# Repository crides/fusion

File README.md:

# Fusion

My travel board. Uses minimum spacing with choc mini (PG1232) and Cirque touchpad. It's meant to be folded for easy packing for traveling/going to classes. It's called fusion because the halves are now "fused" together (all my previous boards have been split).

The following picture shows how it's originally assembled:

You can find the caps [here](https://github.com/crides/sqdg). They are printed with the MJF Nylon process at JLCPCB.

The 2 extra pinky keys on the right side are different because I forgot about them when designing and printing the keycaps. Those keys are for steno, and like [the `fissure`](https://github.com/crides/fissure/) this includes [embedded stenograpy](https://github.com/crides/steno/).

The keymap is basically the same as [on the fissure](https://github.com/crides/fissure/?tab=readme-ov-file#latest-keymap) with a little difference in how the gaming and alternative layout layers are toggled.

One extra small feature it has is a PWM controlled RGB LED, which I use to display [LED widgets](https://github.com/zmkfirmware/zmk/issues/1003) on.

You can find a recent-ish configuration for this board [here](https://github.com/crides/zmk/tree/fusion-led-c-config/).

With the 350mAh battery on the board, this lasted me ~5 months of usage (it could've been even longer, the battery started out not on full charge (~3.8V)).

The board measures 148 x 79.5 x 21mm when it's folded (23mm thick if you include the bumpons, and 133mm long if the last 2 keys are cut off, like in the current state (see the bottom of this page)), which fits into a small bag. I carry this with my Pixel 5a in my big sweatpants pocket for quite a while. I would just go to places, take out the keeb and my phone, unfold it and work with Termux.

All parts are generated from Python, some using [solidff](https://github.com/crides/solidff), some using [CadQuery](https://github.com/CadQuery/cadquery/), depending on when the part was designed. The only parts actually used are `hinge1`, `hinge2` and `touchpad-holder`.

Includes JLCPCB BOM ([`bom.csv`](bom.csv)) and POS ([`pos.csv`](pos.csv)) files for PCBA.

---

Here's the board after almost 11 months of usage (right before 2023):

Main differences:
- The trackpad is in a really weird spot. I knew this in the design phase, but didn't have much idea of how to fix it. So it's taken out. 
- A solar charging circuit with a Li-ion supercapacitor is added, replacing the battery and its charging circuit. The current supercap is 150F (!), which is equivalent to about 40mAh. This was to be done on another version of the board, but a small test circuit was fabbed instead, and that was used here with a fair amount of bodging. Now I can say the fusion board is (well can be) powered by fusion! (a.k.a. solar powered)
- There's a crack on the screen. The adhesive I used didn't cover the whole screen area, and once I pressed on the top left corner too hard, where the adhesive also didn't cover and left some empty space, and it cracked :(.

---

Here it is after 1 year:

Somehow the supercap doesn't seem to do well with the cold, so I swapped to the old small battery. Tried out a larger Cirque touchpad, by basically shifting the screen to the left side though a bunch of wires.

---

Here's what it looks like after 16 months:

The screen's completely broken, with the ribbon cable half "cut" (no idea how that happened). The trackpad location is better, but still pretty useless for my use cases (I use it 95% on top of my laptop keyboard most of the time, and the touchpad is right there, with more ready-to-be-used gestures. So touchpads and solar panels are gone. Nothing interesting to see here...

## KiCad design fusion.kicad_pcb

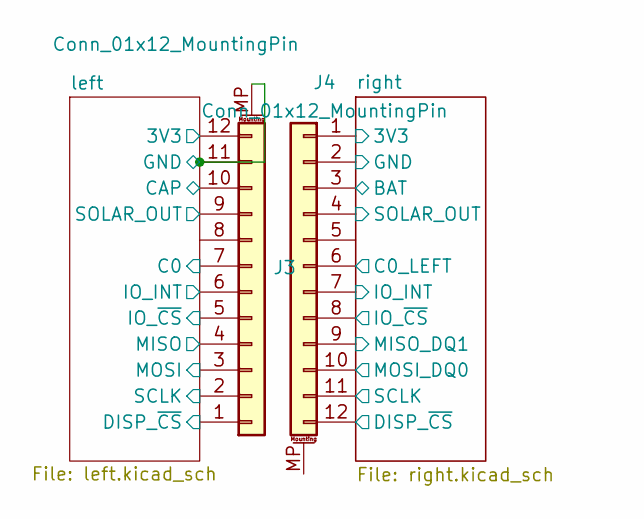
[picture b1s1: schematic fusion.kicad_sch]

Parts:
J3, J4: Conn_01x12_MountingPin; Hirose_FH12-12S-0.5SH_1x12-1MP_P0.50mm_Horizontal

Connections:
/left/3V3: J3.12; also elsewhere on the board
/left/C0: J3.7; also elsewhere on the board
/left/CAP: J3.10; also elsewhere on the board
/left/DISP_~CS: J3.1; also elsewhere on the board
/left/GND: J3.11, J3.MP (MountPin); also elsewhere on the board
/left/IO_INT: J3.6; also elsewhere on the board
/left/IO_~CS: J3.5; also elsewhere on the board
/left/MISO: J3.4; also elsewhere on the board
/left/MOSI: J3.3; also elsewhere on the board
/left/SCLK: J3.2; also elsewhere on the board
/left/SOLAR_OUT: J3.9; also elsewhere on the board
/right/3V3_nRF: J4.1; also elsewhere on the board
/right/BAT: J4.3; also elsewhere on the board
/right/C0_LEFT: J4.6; also elsewhere on the board
/right/DISP_~CS: J4.12; also elsewhere on the board
/right/IO_INT: J4.7; also elsewhere on the board
/right/IO_~CS: J4.8; also elsewhere on the board
/right/MISO_DQ1: J4.9; also elsewhere on the board
/right/MOSI_DQ0: J4.10; also elsewhere on the board
/right/SCLK: J4.11; also elsewhere on the board
/right/SOLAR_OUT: J4.4; also elsewhere on the board
GND: J4.2; also elsewhere on the board

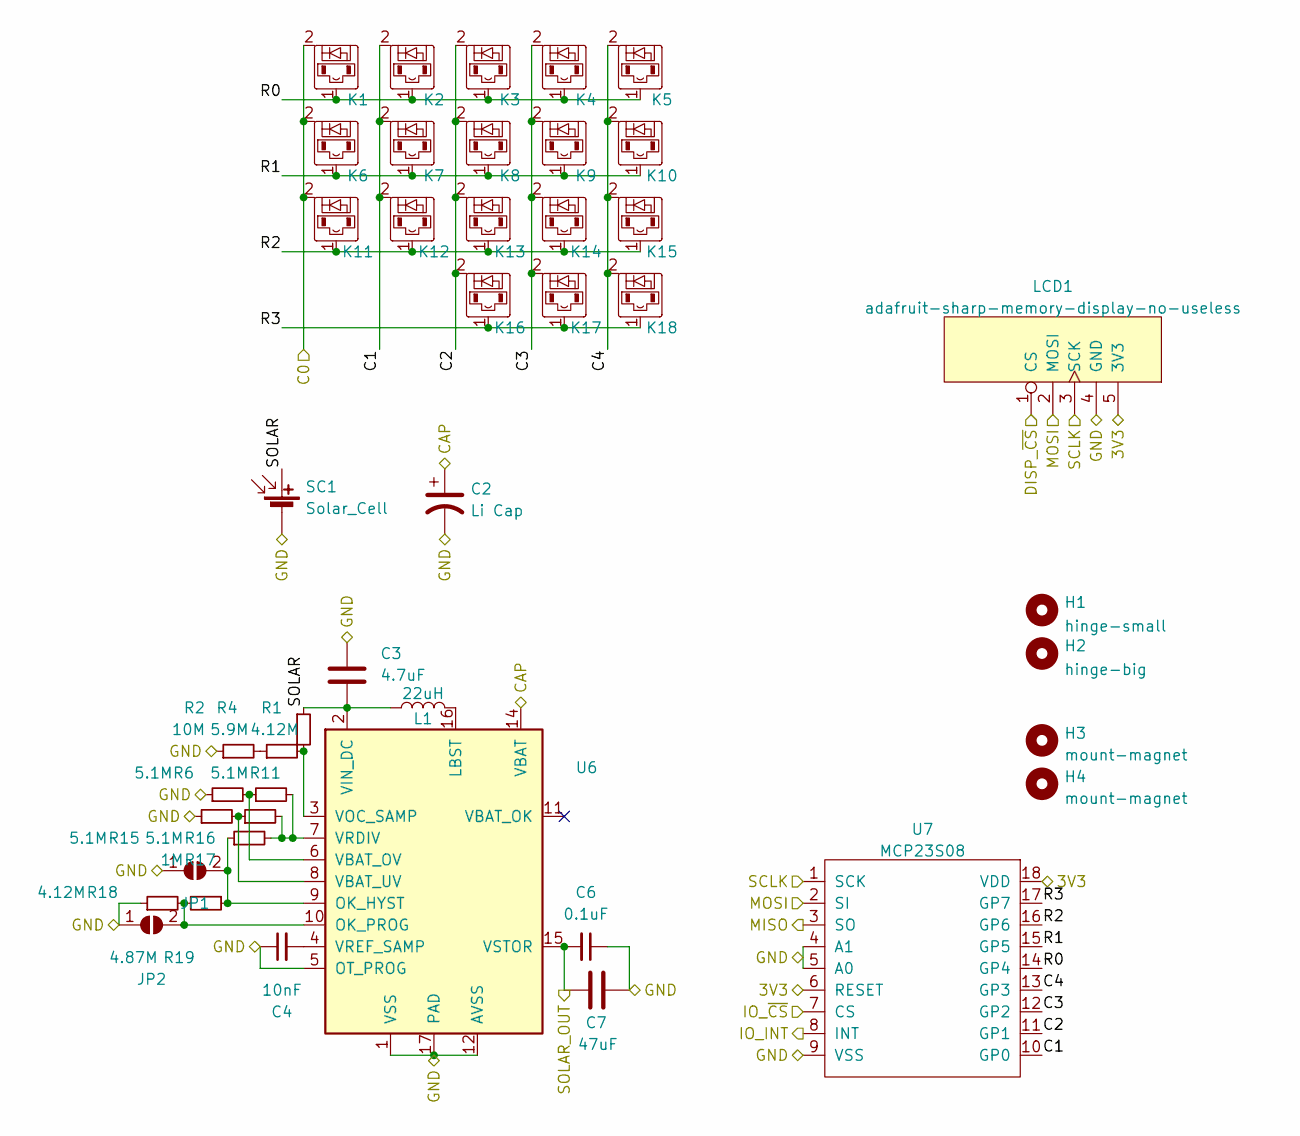
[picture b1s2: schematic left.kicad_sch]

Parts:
C2: Li Cap; CP_Radial_D13.0mm_P5.00mm
C3: 4.7uF; C_0603_1608Metric
C4: 10nF; C_0603_1608Metric
C6: 0.1uF; C_0603_1608Metric
C7: 47uF; C_0805_2012Metric
H1: hinge-small; hinge1
H2: hinge-big; hinge2
H3, H4: mount-magnet; m2-heat-insert-pad
JP1: SolderJumper-2_P1.3mm_Open_RoundedPad1.0x1.5mm
JP2: SolderJumper_2_Open; SolderJumper-2_P1.3mm_Open_RoundedPad1.0x1.5mm
K1, K5, K6, K10, K11, K15: diode-choc; pg1232-DCN
K2, K7, K12: diode-choc; pg1232-DCR
K3, K8, K13, K16, K17, K18: diode-choc; pg1232-DC
K4, K9, K14: diode-choc; pg1232-DCL
L1: 22uH; L_Wuerth_WE-TPC-3816
LCD1: adafruit-sharp-memory-display-no-useless; adafruit-sharp-memory-display-1.3in-no-mounting-no-useless
R1, R18: 4.12M; R_0603_1608Metric
R2: 10M; R_0603_1608Metric
R4: 5.9M; R_0603_1608Metric
R6, R11, R15, R16: 5.1M; R_0603_1608Metric
R17: 1M; R_0603_1608Metric
R19: 4.87M; R_0603_1608Metric
SC1: Solar_Cell; KXOB25-05X3F
U6: QFN-16-1EP_3x3mm_P0.5mm_EP1.7x1.7mm
U7: MCP23S08; SOIC-18W_7.5x11.6mm_P1.27mm

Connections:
/left/3V3: LCD1.5 (3V3), U7.6 (RESET), U7.18 (VDD); also elsewhere on the board
/left/C0: K1.2, K6.2, K11.2; also elsewhere on the board
/left/C1: K2.2, K7.2, K12.2, U7.10 (GP0)
/left/C2: K3.2, K8.2, K13.2, K16.2, U7.11 (GP1)
/left/C3: K4.2, K9.2, K14.2, K17.2, U7.12 (GP2)
/left/C4: K5.2, K10.2, K15.2, K18.2, U7.13 (GP3)
/left/CAP: C2.1, U6.14 (VBAT); also elsewhere on the board
/left/DISP_~CS: LCD1.1 (CS); also elsewhere on the board
/left/GND: C2.2, C3.1, C4.1, C6.1, C7.2, JP1.1 (A), JP2.1 (A), LCD1.4 (GND), R2.1, R6.1, R15.1, R18.1, SC1.2 (-), U6.1 (VSS), U6.5 (OT_PROG), U6.12 (AVSS), U6.13 (VSS), U6.17 (PAD), U7.4 (A1), U7.5 (A0), U7.9 (VSS); also elsewhere on the board
/left/IO_INT: U7.8 (INT); also elsewhere on the board
/left/IO_~CS: U7.7 (CS); also elsewhere on the board
/left/MISO: U7.3 (SO); also elsewhere on the board
/left/MOSI: LCD1.2 (MOSI), U7.2 (SI); also elsewhere on the board
/left/R0: K1.1, K2.1, K3.1, K4.1, K5.1, U7.14 (GP4)
/left/R1: K6.1, K7.1, K8.1, K9.1, K10.1, U7.15 (GP5)
/left/R2: K11.1, K12.1, K13.1, K14.1, K15.1, U7.16 (GP6)
/left/R3: K16.1, K17.1, K18.1, U7.17 (GP7)
/left/SCLK: LCD1.3 (SCK), U7.1 (SCK); also elsewhere on the board
/left/SOLAR: C3.2, L1.1, R1.1, SC1.1 (+), U6.2 (VIN_DC)
/left/SOLAR_OUT: C6.2, C7.1, U6.15 (VSTOR); also elsewhere on the board
unnamed: C4.2, U6.4 (VREF_SAMP)
unnamed: JP1.2 (B), R17.1, R19.1, U6.9 (OK_HYST)
unnamed: JP2.2 (B), R18.2, R19.2, U6.10 (OK_PROG)
unnamed: L1.2, U6.16 (LBST)
unnamed: R1.2, R4.2, U6.3 (VOC_SAMP)
unnamed: R2.2, R4.1
unnamed: R6.2, R11.1, U6.6 (VBAT_OV)
unnamed: R11.2, R16.2, R17.2, U6.7 (VRDIV)
unnamed: R15.2, R16.1, U6.8 (VBAT_UV)

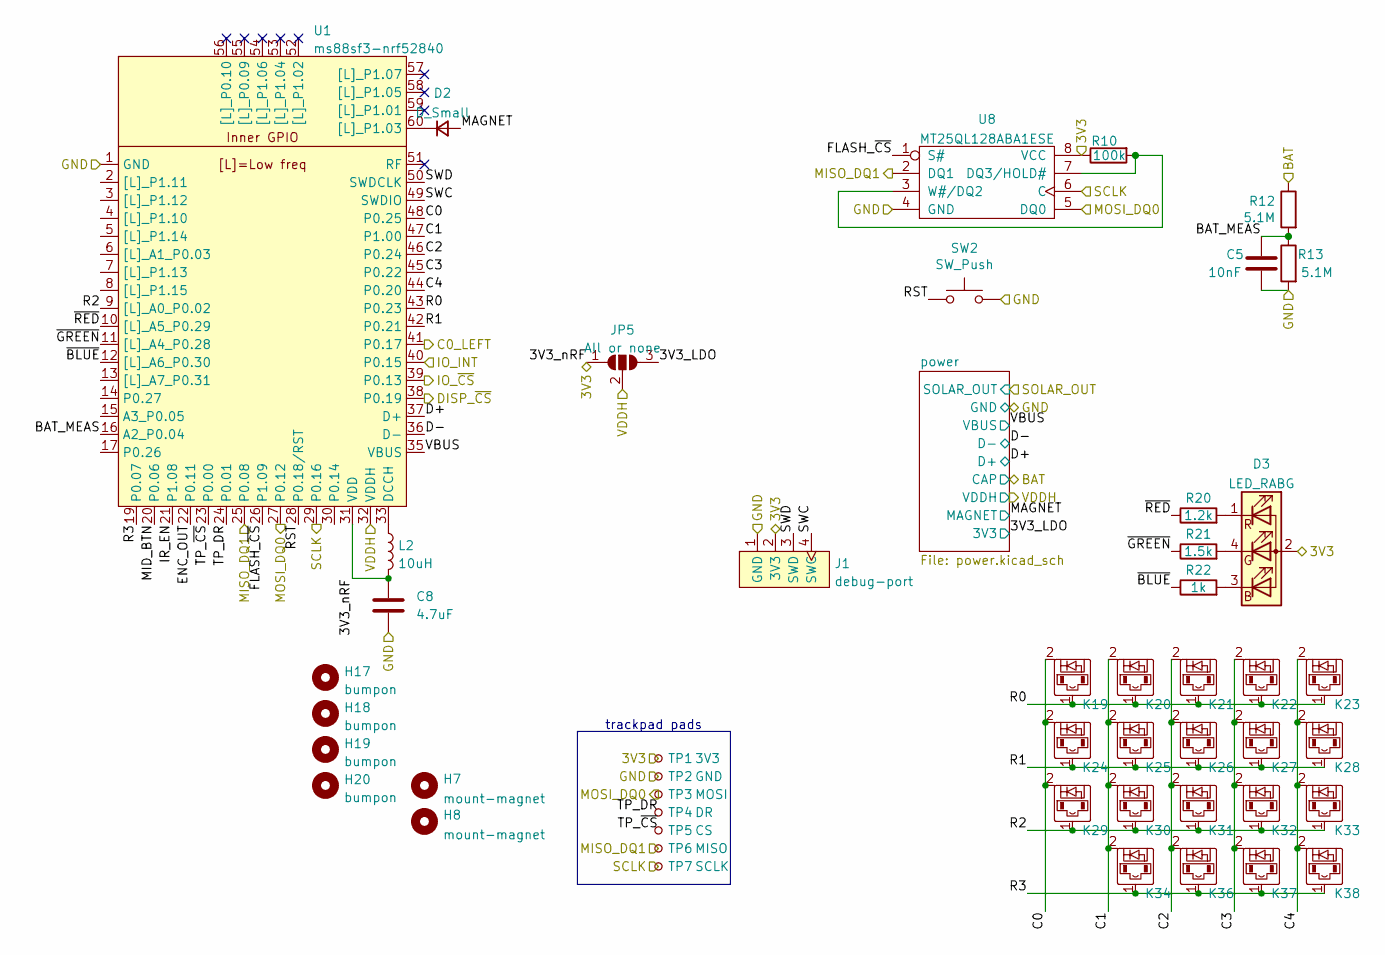
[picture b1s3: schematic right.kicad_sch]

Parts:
C5: 10nF; C_0603_1608Metric
C8: 4.7uF; C_0603_1608Metric
D2: D_Small; D_SOD-123
D3: LED_RABG; LED_ASMB-KTF0-0A306
H7, H8: mount-magnet; m2-heat-insert-pad
H17, H18, H19, H20: bumpon; bumpon-sunk-hole
J1: debug-port; debug-port-single-side
JP5: All or none; SolderJumper-3_P1.3mm_Open_RoundedPad1.0x1.5mm
K19, K23, K24, K28, K29, K33: diode-choc; pg1232-DCN
K20, K25, K30: diode-choc; pg1232-DCL
K21, K26, K31, K36, K37, K38: diode-choc; pg1232-DC
K22, K27, K32: diode-choc; pg1232-DCR
K34: diode-choc; pg1232-DSS
L2: 10uH; L_0603_1608Metric
R10: 100k; R_0603_1608Metric
R12, R13: 5.1M; R_0603_1608Metric
R20: 1.2k; R_0603_1608Metric
R21: 1.5k; R_0603_1608Metric
R22: 1k; R_0603_1608Metric
SW2: SW_Push; SW_SPST_TL3342
TP1: 3V3; TestPoint_THTPad_D1.0mm_Drill0.5mm
TP2: GND; TestPoint_THTPad_D1.0mm_Drill0.5mm
TP3: MOSI; TestPoint_THTPad_D1.0mm_Drill0.5mm
TP4: DR; TestPoint_THTPad_D1.0mm_Drill0.5mm
TP5: CS; TestPoint_THTPad_D1.0mm_Drill0.5mm
TP6: MISO; TestPoint_THTPad_D1.0mm_Drill0.5mm
TP7: SCLK; TestPoint_THTPad_D1.0mm_Drill0.5mm
U1: ms88sf3-nrf52840; ms88sf3
U8: MT25QL128ABA1ESE; SOIC-8_5.23x5.23mm_P1.27mm

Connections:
/right/3V3_LDO: JP5.3 (B); also elsewhere on the board
/right/3V3_nRF: C8.1, D3.2 (A), J1.2 (3V3), JP5.1 (A), L2.2, R10.1, TP1.1, U1.31 (VDD), U8.8 (VCC); also elsewhere on the board
/right/BAT: R12.1; also elsewhere on the board
/right/BAT_MEAS: C5.1, R12.2, R13.1, U1.16 (A2_P0.04)
/right/C0: K19.2, K24.2, K29.2, U1.48 (P0.25)
/right/C0_LEFT: U1.41 (P0.17); also elsewhere on the board
/right/C1: K20.2, K25.2, K30.2, K34.2, U1.47 (P1.00)
/right/C2: K21.2, K26.2, K31.2, K36.2, U1.46 (P0.24)
/right/C3: K22.2, K27.2, K32.2, K37.2, U1.45 (P0.22)
/right/C4: K23.2, K28.2, K33.2, K38.2, U1.44 (P0.20)
/right/D+: U1.37 (D+); also elsewhere on the board
/right/D-: U1.36 (D-); also elsewhere on the board
/right/DISP_~CS: U1.38 (P0.19); also elsewhere on the board
/right/ENC_OUT: U1.22 (P0.11); also elsewhere on the board
/right/FLASH_~CS: U1.26 (P1.09), U8.1 (S#)
/right/IO_INT: U1.40 (P0.15); also elsewhere on the board
/right/IO_~CS: U1.39 (P0.13); also elsewhere on the board
/right/IR_EN: U1.21 (P1.08); also elsewhere on the board
/right/MAGNET: D2.2 (A); also elsewhere on the board
/right/MID_BTN: U1.20 (P0.06); also elsewhere on the board
/right/MISO_DQ1: TP6.1, U1.25 (P0.08), U8.2 (DQ1); also elsewhere on the board
/right/MOSI_DQ0: TP3.1, U1.27 (P0.12), U8.5 (DQ0); also elsewhere on the board
/right/R0: K19.1, K20.1, K21.1, K22.1, K23.1, U1.43 (P0.23)
/right/R1: K24.1, K25.1, K26.1, K27.1, K28.1, U1.42 (P0.21)
/right/R2: K29.1, K30.1, K31.1, K32.1, K33.1, U1.9 ([L]_A0_P0.02)
/right/R3: K34.1, K36.1, K37.1, K38.1, U1.19 (P0.07)
/right/RST: SW2.1, U1.28 (P0.18/RST)
/right/SCLK: TP7.1, U1.29 (P0.16), U8.6 (C); also elsewhere on the board
/right/SWC: J1.4 (SWC), U1.49 (SWDIO)
/right/SWD: J1.3 (SWD), U1.50 (SWDCLK)
/right/TP_DR: TP4.1, U1.24 (P0.01)
/right/TP_~CS: TP5.1, U1.23 (P0.00)
/right/VBUS: U1.35 (VBUS); also elsewhere on the board
/right/VDDH: JP5.2 (C), U1.32 (VDDH); also elsewhere on the board
/right/~BLUE: R22.1, U1.12 ([L]_A6_P0.30)
/right/~GREEN: R21.1, U1.11 ([L]_A4_P0.28)
/right/~RED: R20.1, U1.10 ([L]_A5_P0.29)
GND: C5.2, C8.2, J1.1 (GND), R13.2, SW2.2, TP2.1, U1.1 (GND), U1.18 (GND), U1.34 (GND), U1.61 (GND), U1.62 (GND), U1.63 (GND), U1.64 (GND), U8.4 (GND); also elsewhere on the board
unnamed: D2.1 (K), U1.60 ([L]_P1.03)
unnamed: D3.1 (RK), R20.2
unnamed: D3.3 (BK), R22.2
unnamed: D3.4 (GK), R21.2
unnamed: L2.1, U1.33 (DCCH)
unnamed: R10.2, U8.3 (W#/DQ2), U8.7 (DQ3/HOLD#)

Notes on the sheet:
trackpad pads

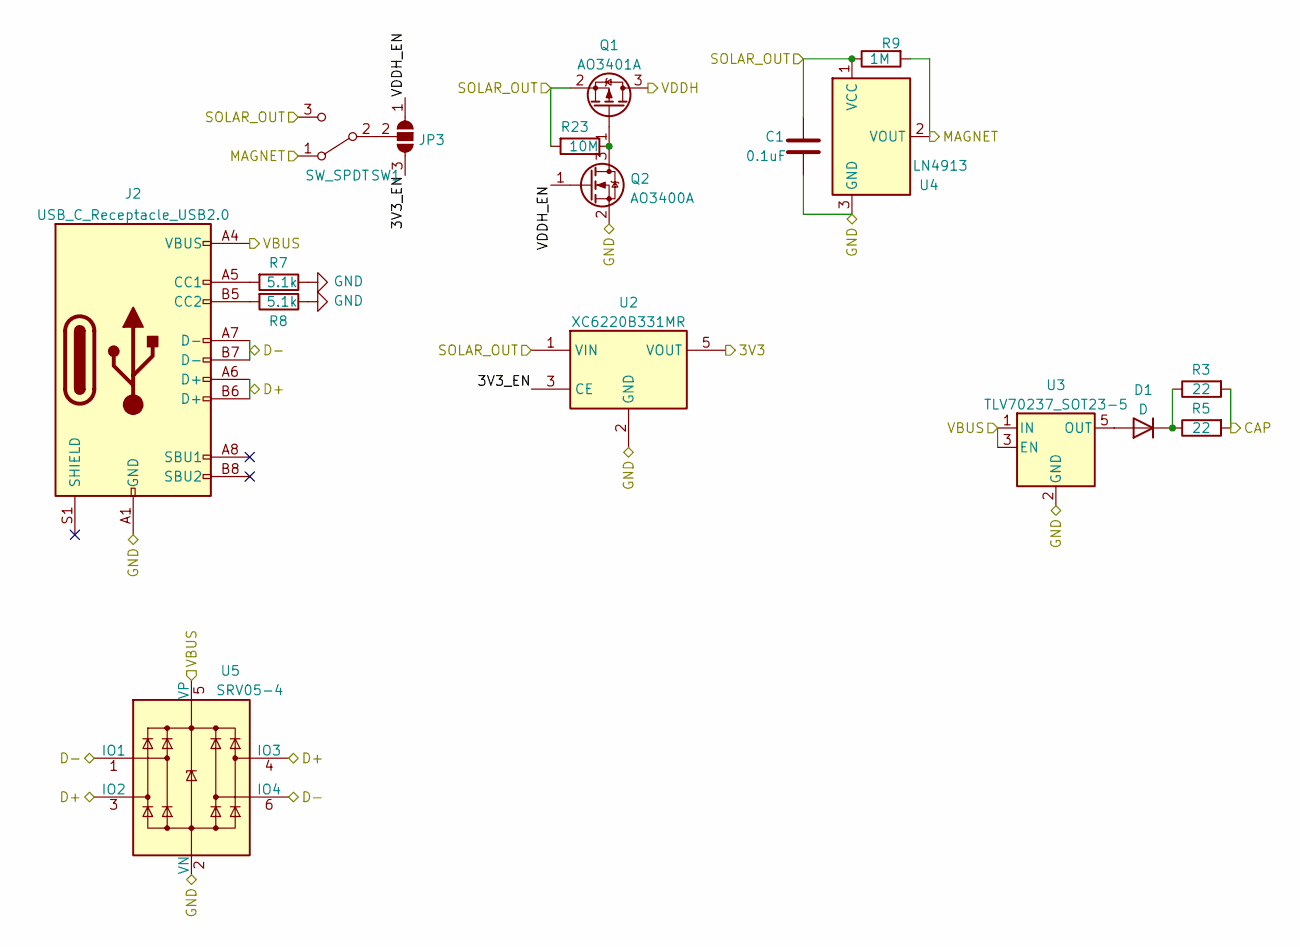
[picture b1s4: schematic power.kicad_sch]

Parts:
C1: 0.1uF; C_0603_1608Metric
D1: D; D_SOD-123
J2: USB_C_Receptacle_USB2.0; USB_C_Receptacle_HRO_TYPE-C-31-M-12
JP3: SolderJumper_3_Open; SolderJumper-3_P1.3mm_Open_RoundedPad1.0x1.5mm
Q1: AO3401A; SOT-23
Q2: AO3400A; SOT-23
R3, R5: 22; R_0603_1608Metric
R7, R8: 5.1k; R_0603_1608Metric
R9: 1M; R_0603_1608Metric
R23: 10M; R_0603_1608Metric
SW1: SW_SPDT; SW_SPDT_PCM12
U2: XC6220B331MR; SOT-23-5
U3: TLV70237_SOT23-5; SOT-23-5
U4: LN4913; SOT-23
U5: SRV05-4; SOT-23-6

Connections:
/right/3V3_LDO: U2.5 (VOUT); also elsewhere on the board
/right/BAT: R3.2, R5.2; also elsewhere on the board
/right/D+: J2.A6 (D+), J2.B6 (D+), U5.3 (IO2), U5.4 (IO3); also elsewhere on the board
/right/D-: J2.A7 (D-), J2.B7 (D-), U5.1 (IO1), U5.6 (IO4); also elsewhere on the board
/right/MAGNET: R9.2, SW1.1 (A), U4.2 (VOUT); also elsewhere on the board
/right/SOLAR_OUT: C1.1, Q1.2 (S), R9.1, R23.2, SW1.3 (C), U2.1 (VIN), U4.1 (VCC); also elsewhere on the board
/right/VBUS: J2.A4 (VBUS), J2.A9 (VBUS), J2.B4 (VBUS), J2.B9 (VBUS), U3.1 (IN), U3.3 (EN), U5.5 (VP); also elsewhere on the board
/right/VDDH: Q1.3 (D); also elsewhere on the board
/right/power/3V3_EN: JP3.3 (B), U2.3 (CE)
/right/power/VDDH_EN: JP3.1 (A), Q2.1 (G)
GND: C1.2, J2.A1 (GND), J2.A12 (GND), J2.B1 (GND), J2.B12 (GND), Q2.2 (S), R7.1, R8.1, U2.2 (GND), U3.2 (GND), U4.3 (GND), U5.2 (VN); also elsewhere on the board
unnamed: D1.1 (K), R3.1, R5.1
unnamed: D1.2 (A), U3.5 (OUT)
unnamed: J2.A5 (CC1), R7.2
unnamed: J2.B5 (CC2), R8.2
unnamed: JP3.2 (C), SW1.2 (B)
unnamed: Q1.1 (G), Q2.3 (D), R23.1

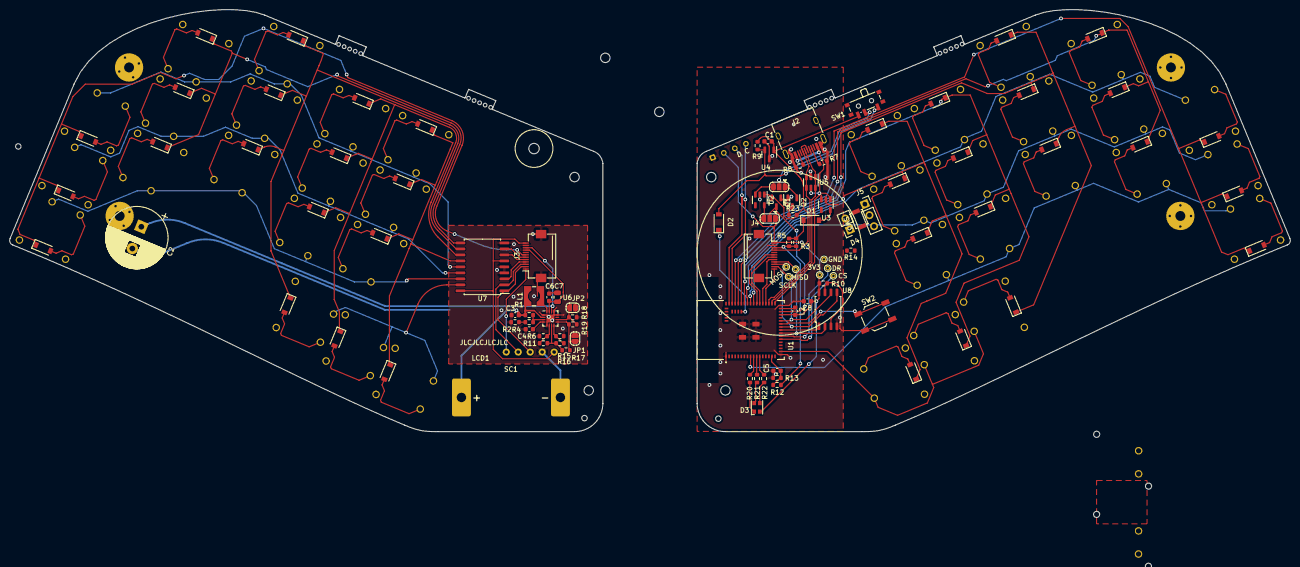
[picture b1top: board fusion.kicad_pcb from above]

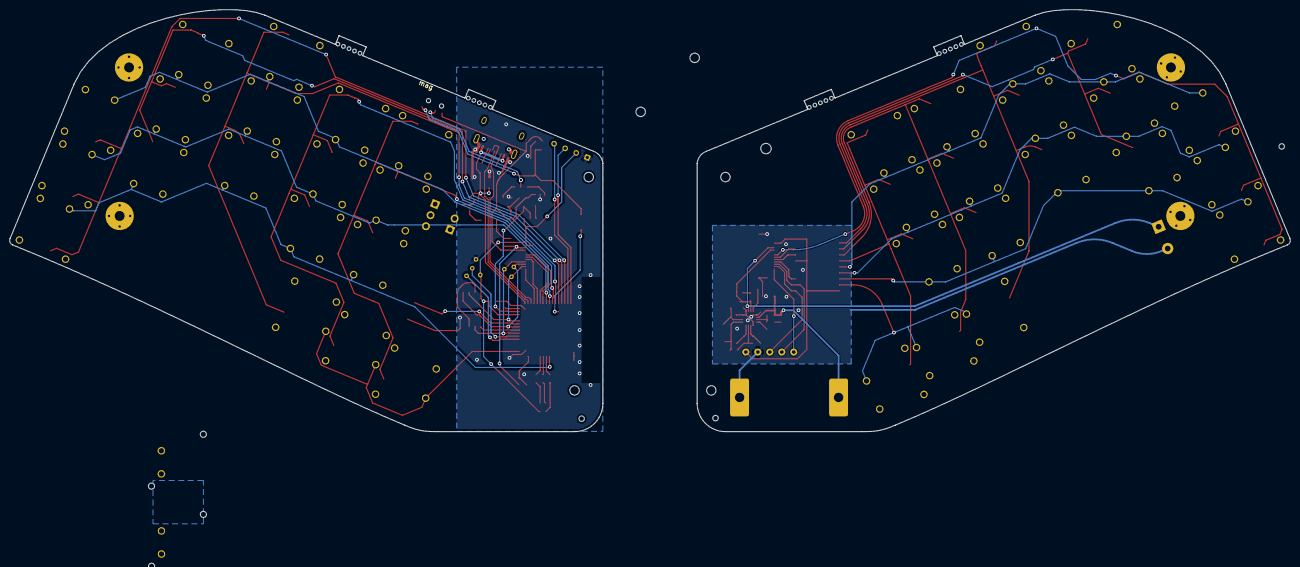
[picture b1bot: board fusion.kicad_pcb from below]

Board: 2 copper layers, 271.7 x 89.5 mm, 117 parts (2 on the bottom side), 83 nets.

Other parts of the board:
D4: LED; PinSocket_1x02_P2.54mm_Vertical
H5: hinge-big; hinge2
H6: hinge-small; hinge1
H9, H10, H11, H12: mouse-bite; breakaway-mousebites
J5: Conn_01x03_Female; PinSocket_1x03_P2.54mm_Vertical
P1: touchpad-holder
R14: 1k; R_0603_1608Metric
SW3: SW_Push; SW_SPST_B3U-1000P

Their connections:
/right/3V3_nRF: D4.2 (A), J5.2; also elsewhere on the board
/right/ENC_OUT: J5.1; also elsewhere on the board
/right/IR_EN: R14.2; also elsewhere on the board
/right/MID_BTN: SW3.2; also elsewhere on the board
GND: J5.3, SW3.1; also elsewhere on the board
unnamed: D4.1 (K), R14.1

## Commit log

2021-07-31 before hinges
2021-08-01 fpc and hinges
2021-08-15 trackpad
2021-08-15 update chocs
2021-08-16 use narrower pinky spacing
2021-09-17 final?
2021-09-26 backup
2021-10-03 Hydrogen.PCB
    - add Adafruit CAD files for Sharp display
    - convert to all 3D printed mechanical parts
    - update part dimensions to lowest estimate
2021-10-15 Hydrogen.Parts
2021-10-17 fix gerber issue
    This is just to generate a set of Gerbers so that people can print (if
    anyone does) the correct version easily. NOT TESTED
2022-01-07 update libs
2022-01-07 update models
2022-01-07 update PCB
    use cirque trackpad, increase angle to 22.5
2022-01-07 fix(model): remove top bit from cylinder
2022-01-08 add assembly tooling hole
2022-01-09 production version
2022-02-03 v2 parts
2022-03-17 add readme
2023-06-29 Use cq for cover generation
2023-06-29 new version
2023-06-29 shell & adhesive cutting lines for the back
2023-07-11 more pics
2024-08-08 info for pocket keeb competition; fix hinge2
2024-08-08 backup & remove useless things
2025-10-29 right
